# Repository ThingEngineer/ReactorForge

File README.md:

============

This repository contains hardware designs, board schematics, firmware, and software for ReactorForge, an open source high power induction heater platform.

Updates, polls, etc. on this project are being posted on the new Patreon page: [ReactorForge on Patreon](https://www.patreon.com/ReactorForge). You can also support the future of this project there as well.

For project status, official blog, and information about hardware availability visit [ReactorForge.com](https://reactorforge.com/) and be sure to read the [ReactorForge Wiki](https://github.com/joshcam/ReactorForge/wiki).

(photo: assembly of the beta ReactorCore, ReactorForge CriticalMass control board)

principal author: Joshua Campbell josh.lee.campbell@gmail.com

## Project Description
The ReactorForge project is an open source hardware platform for high power induction heating, designed for heavy use and reliable performance in real world applications.

Using fewer discreet components than most commercial induction heaters, the ReactorForge has less failure points and is easy to assemble. It is an open source project with all plans, schematics and code available under the creative commons BY-SA 4.0 license. This not only benefits the maker community and improves future designs but also makes self repair a possibility for those who have purchased kits, rather than relying on expensive factory repairs to proprietary commercial units.

The ReactorForge will be made available in a raw kit form and an ARU (Almost Ready to Use) kit that can be assembled in just a couple hours. Learn about high power electronics while building an awesome machine. The same systems in an induction heater also drive many of todays modern advances such as electric vehicles, renewable energy power inverters, cutting edge research equipment, and much more. Whether your goals are academic or you want to start using an induction heater today the ReactorForge project brings that within reach.

The ReactorForge costs thousands less than equivalent commercial models with features that are not available anywhere else. It has an easy one button/pedal interface for those that want simple to use set and forget type operation. But for those that want full control there are powerful features that let you monitor and regulate operation based on virtually any parameter. And since the entire platform is open source you have a head start to hacking the core (main control board).

(video: Test run of the ReactorForge : CriticalMass +15Kw platform)

## Safety Notice and Disclaimer
An induction heater is a high power device that should be treated with hazards similar but not limited to that of induction cooktops and welders. In addition to that, the following safety guidelines should be observed:

* Don't wear metal jewelry, especially rings near the work coil. Heating can occur a few inches from the coil depending on its geometry.
* Be cautious if you have metal implants, they too could heat up if held near the work coil.
* If you have a pacemaker or other medical implants never use or be near this machine while it is in operation.
* Keep electronics at least 12 inches from the work coil while in operation to avoid damage to these devices.
* Never touch the work coil. Although it is isolated from dangerous mains current, there is still high power present. Holding metal objects that touch or short out the work coil will not harm the unit.
* Wear appropriate PPE, including but not limited to safety glasses and gloves.

We hold no responsibility or liability for injury to person or damage to property should you choose to build and operate one of these machines. If you feel you are not qualified to build or operate an induction heater find someone qualified and willing to assist you.

## Open Source
  <br />This work is licensed under a <a rel="license" href="http://creativecommons.org/licenses/by-sa/4.0/">Creative Commons Attribution-ShareAlike 4.0 International License</a>.

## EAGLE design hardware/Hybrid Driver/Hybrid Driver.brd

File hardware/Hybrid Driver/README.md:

ReactorForge - Hybrid Driver
============

This directory contains the schematic and board file for Hybrid Driver, a dual IGBT module gate driver based on the Powerex M57962L hybrid IC.

See the Wiki for [Documentation](https://github.com/joshcam/ReactorForge/wiki/ReactorForge-Hybrid-Driver)

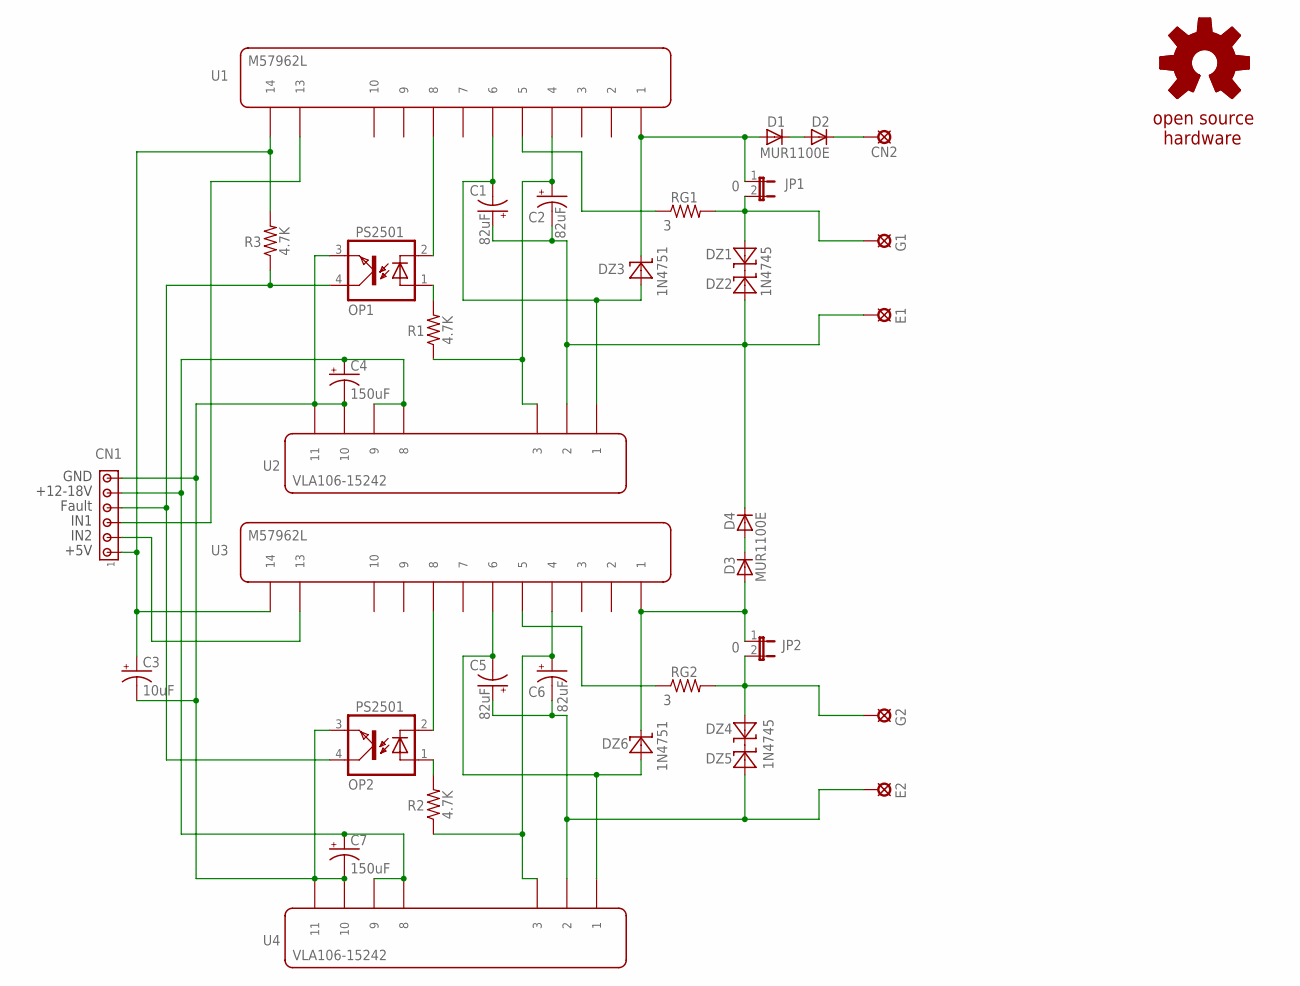
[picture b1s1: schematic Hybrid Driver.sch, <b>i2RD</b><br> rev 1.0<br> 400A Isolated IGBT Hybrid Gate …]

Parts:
C1, C2, C5, C6: 82uF; E2,5-7
C3: 10uF; E2-5
C4, C7: 150uF; E5-8,5
CN1: MTA100-6; 10X06MTA
CN2: SE14
D1, D2, D3, D4: MUR1100E; DO07
DZ1, DZ2, DZ4, DZ5: 1N4745; DIODE.4-AXIAL
DZ3, DZ6: 1N4751; DIODE.4-AXIAL
E1, E2: IGBT-PAD
G1, G2: IGBT-PAD
GOLD_ORB_SM1: OSHWLOGOLOGO8MM; OSHW_8MM
JP1, JP2: 0; JP1
OP1, OP2: PS2501; DIL04
R1, R2, R3: 4.7K; 0207/10
RG1, RG2: 3; 0309/12
U1, U3: M57962L; HYBRID-IC-IBGT-GATE-DRIVER
U2, U4: VLA106-15242; ISOLATED_DC_DC_CONVERTER

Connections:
G1: DZ1.A, G1.1, G1.2, G1.3, G1.4, G1.5, G1.6, JP1.2, RG1.2
G2: DZ4.A, G2.1, G2.2, G2.3, G2.4, G2.5, G2.6, JP2.2, RG2.2
GND: C3.-, C4.-, C7.-, CN1.1 (6), OP1.3 (EMIT), OP2.3 (EMIT), U2.10, U2.11, U4.10, U4.11
GND-E1: C1.+, C2.-, D4.C, DZ2.A, E1.1, E1.2, E1.3, E1.4, E1.5, E1.6, U2.2
GND-E2: C5.+, C6.-, DZ5.A, E2.1, E2.2, E2.3, E2.4, E2.5, E2.6, U4.2
unnamed: D1.C, D2.A
unnamed: CN2.MP, D2.C
unnamed: D1.A, DZ3.C, JP1.1, U1.1
unnamed: OP2.1 (A), R2.2
unnamed: DZ1.C, DZ2.C
unnamed: DZ4.C, DZ5.C
unnamed: C3.+, CN1.6 (1), R3.2, U1.14, U3.14
unnamed: OP2.2 (C), U3.8
unnamed: OP1.2 (C), U1.8
unnamed: OP1.1 (A), R1.2
unnamed: CN1.3 (4), OP1.4 (COL), OP2.4 (COL), R3.1
unnamed: C5.-, DZ6.A, U3.6, U4.1
unnamed: C1.-, DZ3.A, U1.6, U2.1
unnamed: C2.+, R1.1, U1.4, U2.3
unnamed: RG2.1, U3.5
unnamed: C6.+, R2.1, U3.4, U4.3
unnamed: RG1.1, U1.5
unnamed: D3.A, DZ6.C, JP2.1, U3.1
unnamed: D3.C, D4.A
unnamed: C4.+, C7.+, CN1.2 (5), U2.8, U2.9, U4.8, U4.9
unnamed: CN1.4 (3), U1.13
unnamed: CN1.5 (2), U3.13

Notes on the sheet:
GND
+12-18V
Fault
IN1
IN2
+5V

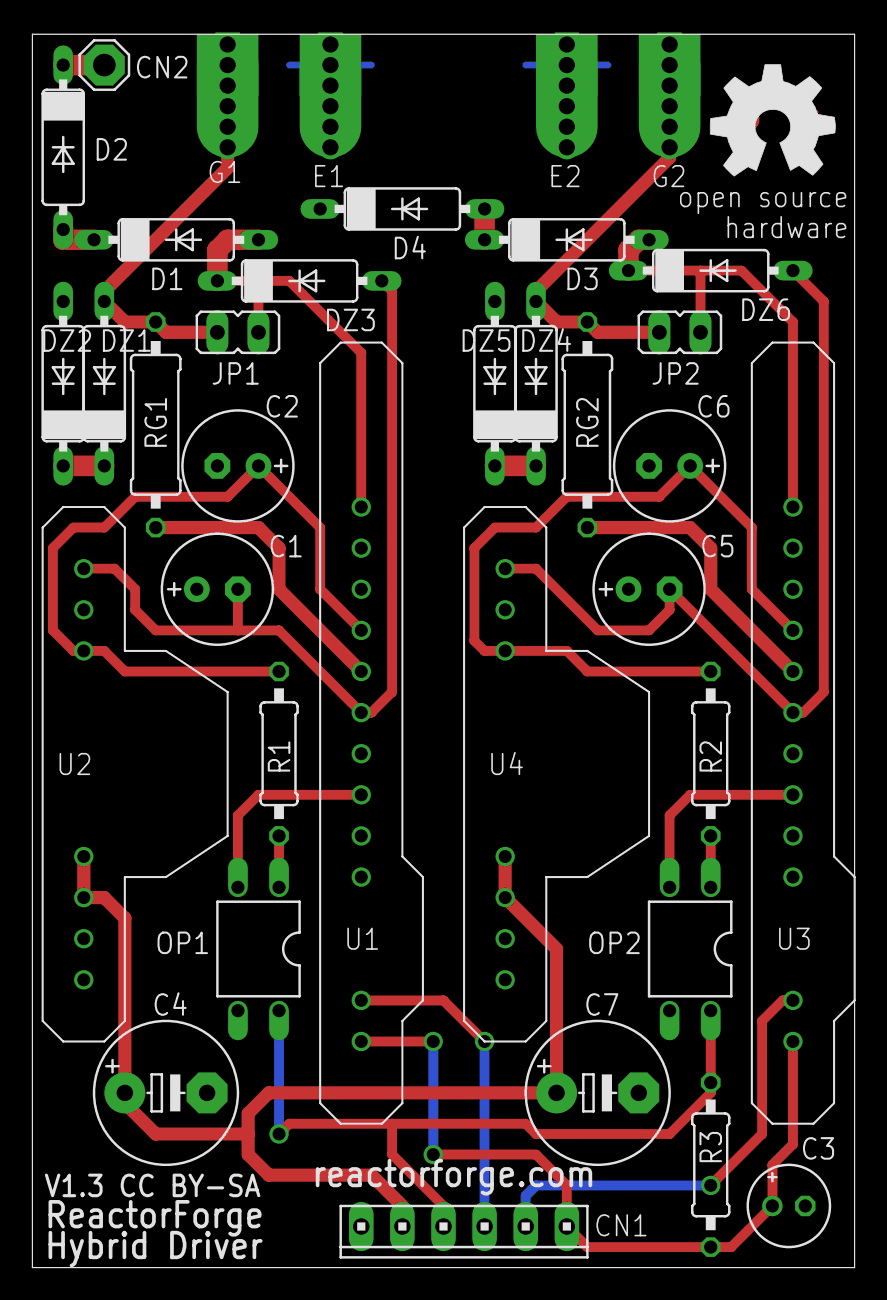
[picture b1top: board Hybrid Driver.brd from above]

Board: 2 copper layers, 50.8 x 76.2 mm, 37 parts (0 on the bottom side), 27 nets.

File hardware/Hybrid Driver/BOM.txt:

Partlist

Exported from Hybrid Driver.brd at 12/30/17 5:46 PM

EAGLE Version 8.5.1 Copyright (c) 1988-2017 Autodesk, Inc.

Assembly variant: 

Part     Value          Package                    Library     Position (inch)       Orientation

C1       82uF           E2,5-7                     resistor    (0.45 1.65)           R0
C2       82uF           E2,5-7                     resistor    (0.5 1.95)            R180
C3       10uF           E2-5                       rcl         (1.84 0.15)           R0
C4       150uF          E5-8,5                     resistor    (0.325 0.425)         R0
C5       82uF           E2,5-7                     resistor    (1.5 1.65)            R0
C6       82uF           E2,5-7                     resistor    (1.55 1.95)           R180
C7       150uF          E5-8,5                     resistor    (1.375 0.425)         R0
CN1      MTA100-6       10X06MTA                   con-amp     (1.05 0.1)            R180
CN2      SE14           SE14                       solpad      (0.175 2.925)         R0
D1       MUR1100E       DO07                       diode       (0.35 2.5)            R0
D2       MUR1100E       DO07                       diode       (0.075 2.725)         R270
D3       MUR1100E       DO07                       diode       (1.3 2.5)             R0
D4       MUR1100E       DO07                       diode       (0.9 2.6)             R0
DZ1      1N4745         DIODE.4-AXIAL              1-Custom    (0.175 2.15)          R90
DZ2      1N4745         DIODE.4-AXIAL              1-Custom    (0.075 2.15)          R90
DZ3      1N4751         DIODE.4-AXIAL              1-Custom    (0.65 2.4)            R0
DZ4      1N4745         DIODE.4-AXIAL              1-Custom    (1.225 2.15)          R90
DZ5      1N4745         DIODE.4-AXIAL              1-Custom    (1.125 2.15)          R90
DZ6      1N4751         DIODE.4-AXIAL              1-Custom    (1.65 2.425)          R0
E1       IGBT-PAD       IGBT-PAD                   1-Custom    (0.725 2.775)         R0
E2       IGBT-PAD       IGBT-PAD                   1-Custom    (1.3 2.775)           R0
G1       IGBT-PAD       IGBT-PAD                   1-Custom    (0.475 2.775)         R0
G2       IGBT-PAD       IGBT-PAD                   1-Custom    (1.55 2.775)          R0
JP1      0              JP1                        jumper      (0.5 2.275)           R90
JP2      0              JP1                        jumper      (1.575 2.275)         R90
OP1      PS2501         DIL04                      optocoupler (0.55 0.775)          R180
OP2      PS2501         DIL04                      optocoupler (1.6 0.775)           R180
R1       4.7K           0207/10                    resistor    (0.6 1.25)            R270
R2       4.7K           0207/10                    resistor    (1.65 1.25)           R270
R3       4.7K           0207/10                    resistor    (1.65 0.25)           R270
RG1      3              0309/12                    resistor    (0.3 2.05)            R90
RG2      3              0309/12                    resistor    (1.35 2.05)           R90
U1       M57962L        HYBRID-IC-IBGT-GATE-DRIVER 1-Custom    (0.65 2.25)           R270
U2       VLA106-15242   ISOLATED_DC_DC_CONVERTER   1-Custom    (-0.025 1.85)         R270
U3       M57962L        HYBRID-IC-IBGT-GATE-DRIVER 1-Custom    (1.7 2.25)            R270
U4       VLA106-15242   ISOLATED_DC_DC_CONVERTER   1-Custom    (1 1.85)              R270

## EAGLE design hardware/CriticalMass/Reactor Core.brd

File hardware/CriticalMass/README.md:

ReactorForge - CriticalMass
============

CriticalMass is the general purpose base unit. Built to run on 240V single phase and be usable on a practical level with large work pieces.

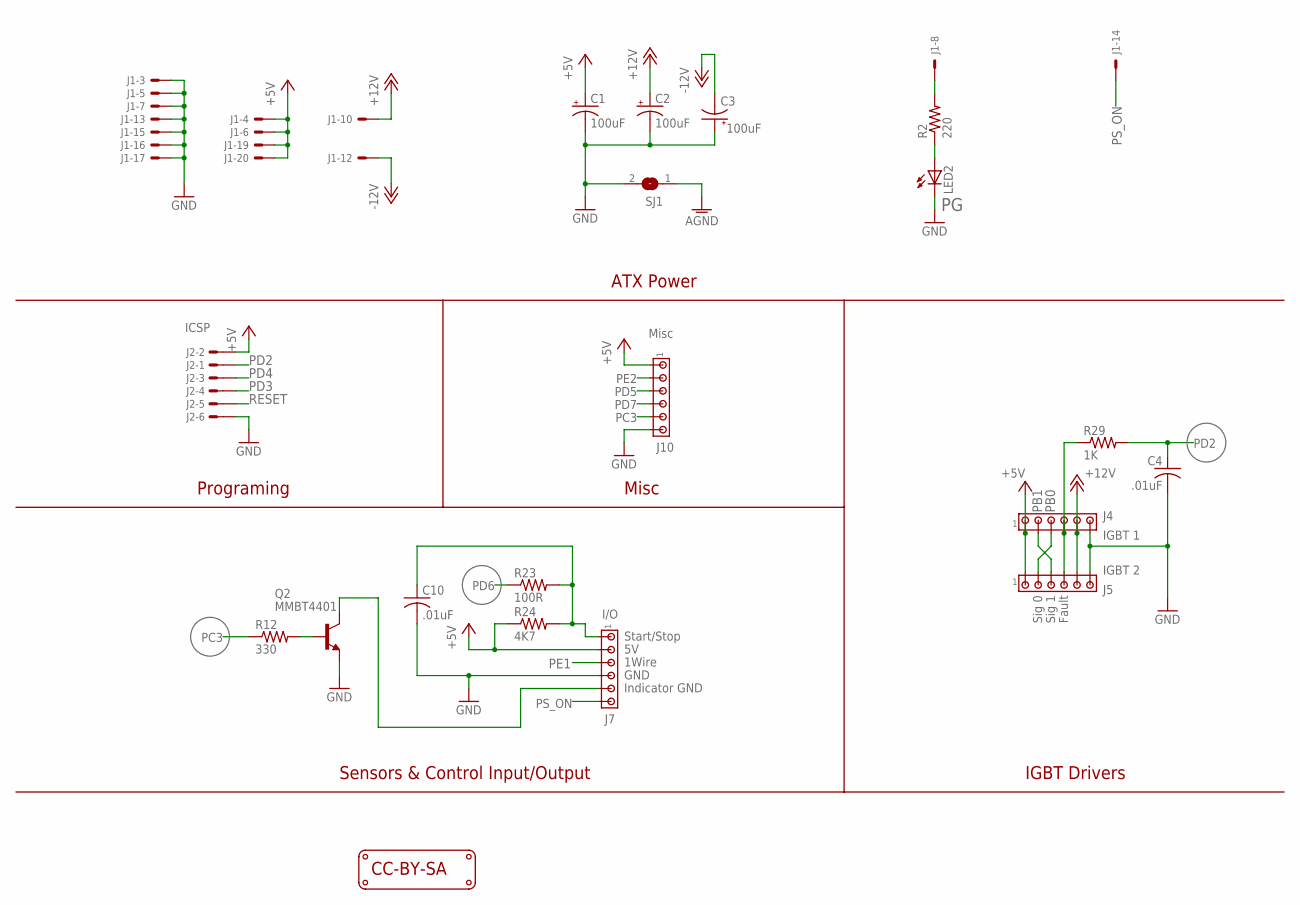
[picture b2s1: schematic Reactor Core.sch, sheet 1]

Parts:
C1, C2, C3: 100uF; E2-5
C4: .01uF; C1206
C10: .01uF; C1206K
J1: ATX Power; 5566-20; MPN 39-29-9206
J2: ICSP; 057-006-1
J4: IGBT 1; 10X06MTA
J5: IGBT 2; 10X06MTA
J7: I/O; 10X06MTA
J10: Misc; 10X06MTA
LED2: LEDCHIPLED_1206; CHIPLED_1206
LOGO1: LOGO_CC-BY-SA
Q2: MMBT4401; SOT23
R2: 220; R1206
R12: 330; R1206
R23: 100R; R1206
R24: 4K7; R1206
R29: 1K; R1206
SJ1: 0; SJ

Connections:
+5V: C1.+, J1.4, J1.6, J1.19, J1.20, J2.2, J4.6 (1), J5.6 (1), J7.5 (2), J10.6 (1), R24.1; also elsewhere on the board
+12V: C2.+, J1.10, J4.2 (5), J5.2 (5); also elsewhere on the board
-12V: C3.-, J1.12; also elsewhere on the board
AGND: SJ1.1; also elsewhere on the board
FAULT: J4.3 (4), J5.3 (4), R29.1
GND: C1.-, C2.-, C3.+, C4.2, C10.2, J1.3, J1.5, J1.7, J1.13, J1.15, J1.16, J1.17, J2.6, J4.1 (6), J5.1 (6), J7.3 (4), J10.1 (6), LED2.C, Q2.2 (E), SJ1.2; also elsewhere on the board
unnamed: LED2.A, R2.1
unnamed: J7.2 (5), Q2.3 (C)
unnamed: Q2.1 (B), R12.2
unnamed: C10.1, J7.6 (1), R23.2, R24.2
PB0: J4.4 (3), J5.5 (2); also elsewhere on the board
PB1: J4.5 (2), J5.4 (3); also elsewhere on the board
PC3: J10.2 (5), R12.1; also elsewhere on the board
PD2: C4.1, J2.1, R29.2; also elsewhere on the board
PD3: J2.4; also elsewhere on the board
PD4: J2.3; also elsewhere on the board
PD5: J10.4 (3); also elsewhere on the board
PD6: R23.1; also elsewhere on the board
PD7: J10.3 (4); also elsewhere on the board
PE1: J7.4 (3); also elsewhere on the board
PE2: J10.5 (2); also elsewhere on the board
PG: J1.8, R2.2
PS_ON: J1.14, J7.1 (6)
RESET: J2.5; also elsewhere on the board

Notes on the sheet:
ATX Power
Programing
Sensors & Control Input/Output
Start/Stop
1Wire
Indicator GND
Misc
GND
IGBT Drivers
Fault
Sig 1
Sig 0

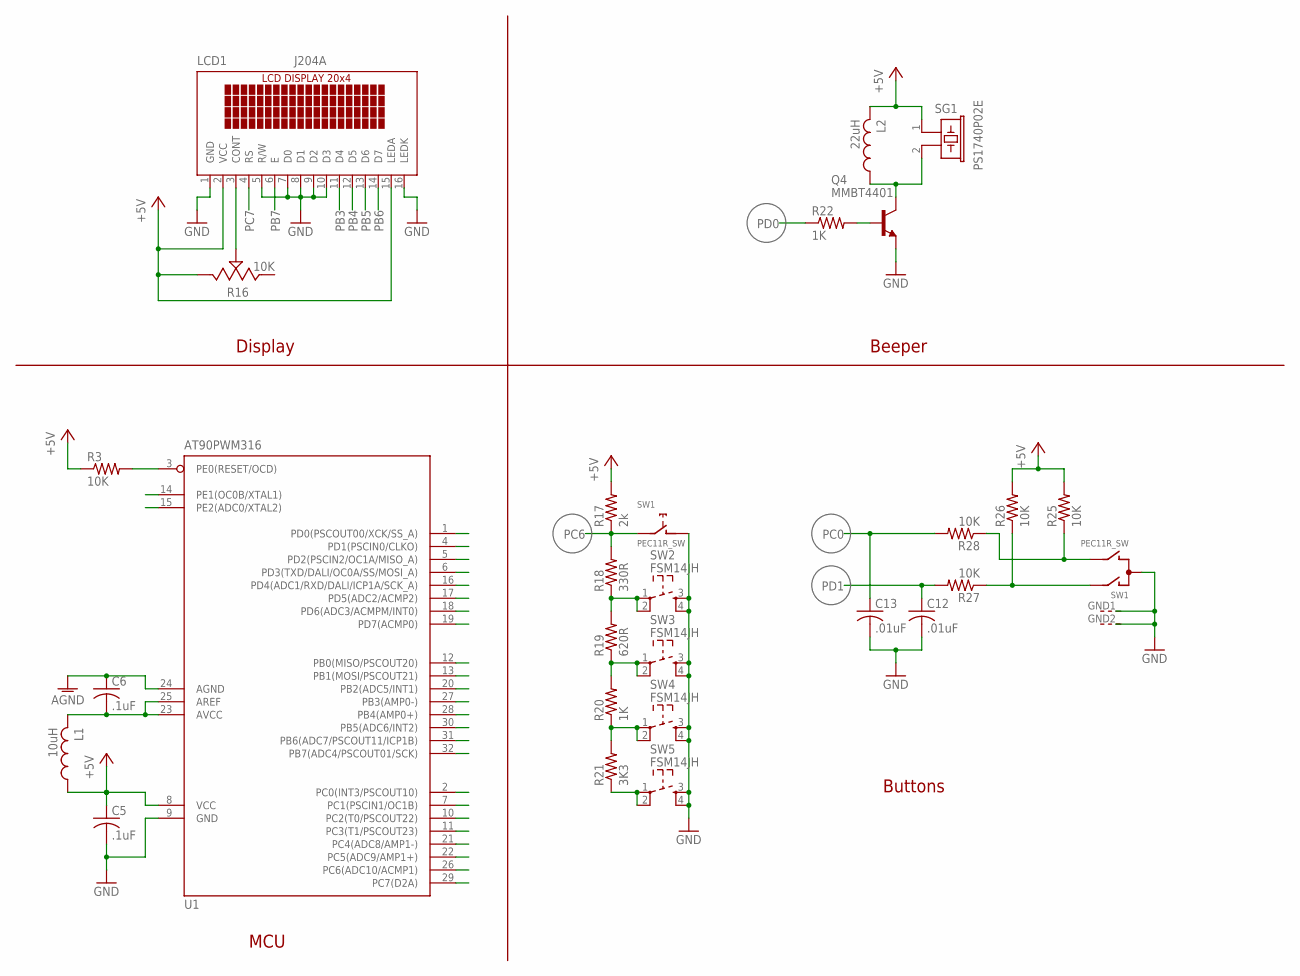
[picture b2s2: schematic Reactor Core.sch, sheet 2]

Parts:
C5, C6: .1uF; C1206K
C12, C13: .01uF; C1206K
L1: 10uH; L3225P
L2: 22uH; L3225P
LCD1: J204A; LCD-20X4
Q4: MMBT4401; SOT23
R3, R27, R28: 10K; R1206
R16: 10K; TRIMMER_3314G
R17: 2k; R1206
R18: 330R; R1206
R19: 620R; R1206
R20, R22: 1K; R1206
R21: 3K3; R1206
R25, R26: 10K; M1206
SG1: PS1740P02E; F/EE17P; MPN PS1740P02E
SW1: PEC11R_SW; BOURNS_PEC11R_SW
SW2, SW3, SW4, SW5: FSM14JH; SW_TACTILE_TOP_ACTIVATED
U1: AT90PWM316; SOIC-32

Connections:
+5V: C5.1, L1.1, L2.2, LCD1.2 (VCC), LCD1.15 (LEDA), R3.1, R16.3, R17.2, R25.2, R26.2, SG1.1, U1.8 (VCC); also elsewhere on the board
AGND: C6.1, U1.24 (AGND); also elsewhere on the board
AVCC: C6.2, L1.2, U1.23 (AVCC), U1.25 (AREF)
GND: C5.2, C12.2, C13.2, LCD1.1 (GND), LCD1.5 (R/W), LCD1.7 (D0), LCD1.8 (D1), LCD1.9 (D2), LCD1.10 (D3), LCD1.16 (LEDK), Q4.2 (E), SW1.C, SW1.GND1 (G), SW1.GND2 (G), SW1.S (1), SW2.3, SW2.4, SW3.3, SW3.4, SW4.3, SW4.4, SW5.3, SW5.4, U1.9 (GND); also elsewhere on the board
unnamed: LCD1.3 (CONT), R16.2
unnamed: L2.1, Q4.3 (C), SG1.2
unnamed: Q4.1 (B), R22.2
unnamed: R25.1, R28.1, SW1.B
unnamed: R26.1, R27.1, SW1.A
unnamed: R21.1, SW5.1, SW5.2
unnamed: R18.1, R19.2, SW2.1, SW2.2
unnamed: R19.1, R20.2, SW3.1, SW3.2
unnamed: R20.1, R21.2, SW4.1, SW4.2
PB0: U1.12 (PB0(MISO/PSCOUT20)); also elsewhere on the board
PB1: U1.13 (PB1(MOSI/PSCOUT21)); also elsewhere on the board
PB2: U1.20 (PB2(ADC5/INT1)); also elsewhere on the board
PB3: LCD1.11 (D4), U1.27 (PB3(AMP0-))
PB4: LCD1.12 (D5), U1.28 (PB4(AMP0+))
PB5: LCD1.13 (D6), U1.30 (PB5(ADC6/INT2))
PB6: LCD1.14 (D7), U1.31 (PB6(ADC7/PSCOUT11/ICP1B))
PB7: LCD1.6 (E), U1.32 (PB7(ADC4/PSCOUT01/SCK))
PC0: C13.1, R28.2, U1.2 (PC0(INT3/PSCOUT10))
PC1: U1.7 (PC1(PSCIN1/OC1B)); also elsewhere on the board
PC2: U1.10 (PC2(T0/PSCOUT22)); also elsewhere on the board
PC3: U1.11 (PC3(T1/PSCOUT23)); also elsewhere on the board
PC4: U1.21 (PC4(ADC8/AMP1-)); also elsewhere on the board
PC5: U1.22 (PC5(ADC9/AMP1+)); also elsewhere on the board
PC6: R17.1, R18.2, SW1.W (2), U1.26 (PC6(ADC10/ACMP1))
PC7: LCD1.4 (RS), U1.29 (PC7(D2A))
PD0: R22.1, U1.1 (PD0(PSCOUT00/XCK/SS_A))
PD1: C12.1, R27.2, U1.4 (PD1(PSCIN0/CLKO))
PD2: U1.5 (PD2(PSCIN2/OC1A/MISO_A)); also elsewhere on the board
PD3: U1.6 (PD3(TXD/DALI/OC0A/SS/MOSI_A)); also elsewhere on the board
PD4: U1.16 (PD4(ADC1/RXD/DALI/ICP1A/SCK_A)); also elsewhere on the board
PD5: U1.17 (PD5(ADC2/ACMP2)); also elsewhere on the board
PD6: U1.18 (PD6(ADC3/ACMPM/INT0)); also elsewhere on the board
PD7: U1.19 (PD7(ACMP0)); also elsewhere on the board
PE1: U1.14 (PE1(OC0B/XTAL1)); also elsewhere on the board
PE2: U1.15 (PE2(ADC0/XTAL2)); also elsewhere on the board
RESET: R3.2, U1.3 (PE0(RESET/OCD)); also elsewhere on the board

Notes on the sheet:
MCU
Display
Buttons
Beeper

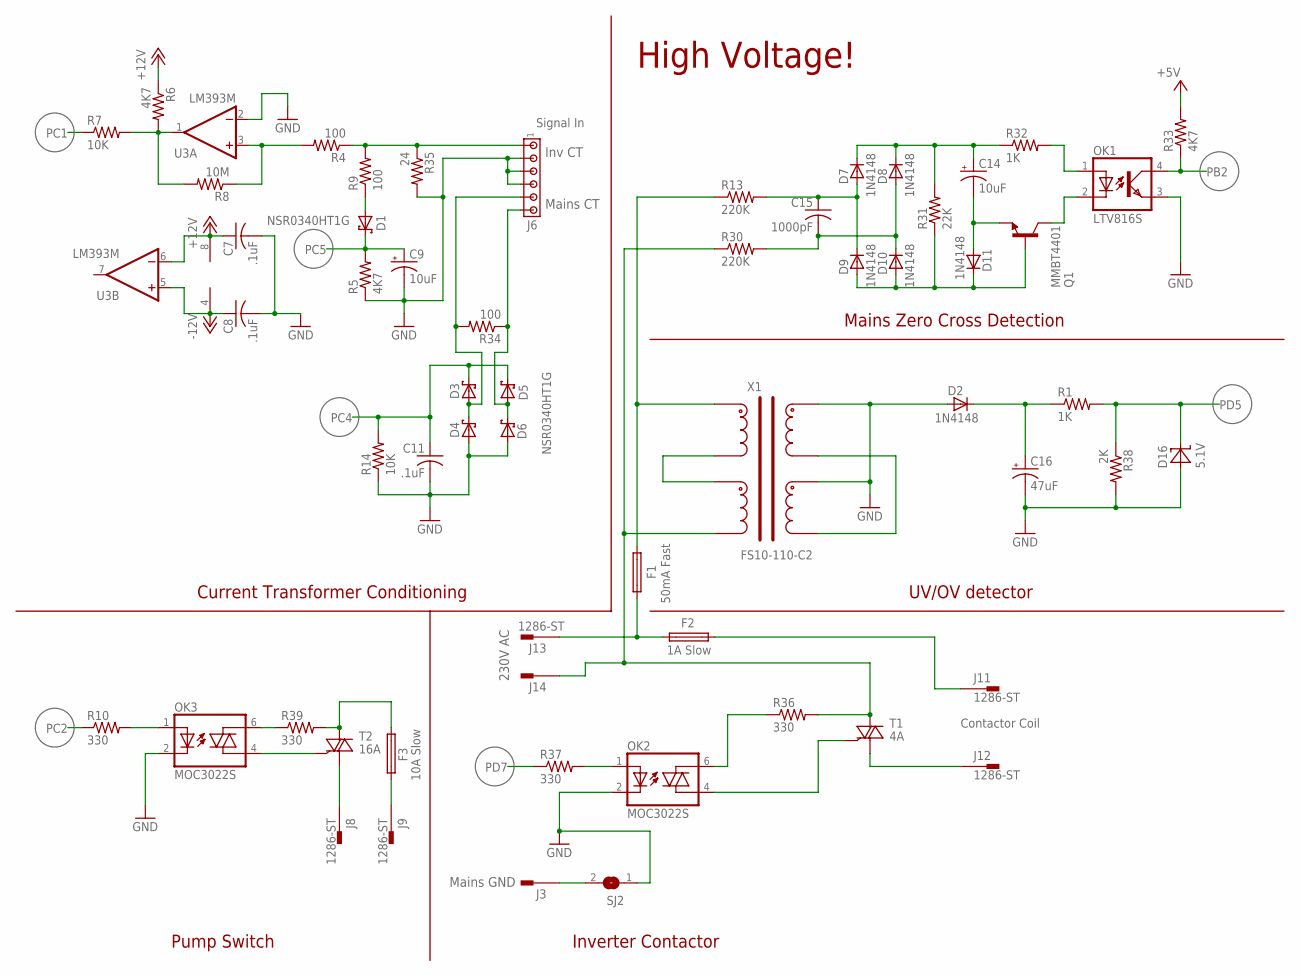
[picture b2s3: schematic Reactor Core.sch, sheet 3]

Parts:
C7, C8, C11: .1uF; C1206
C9, C14: 10uF; 153CLV-0405
C15: 1000pF; C1206
C16: 47uF; 153CLV-0605
D1, D3, D4, D5, D6: NSR0340HT1G; SOD-323
D2, D7, D8, D9, D10, D11: 1N4148; SOD-123
D16: 5.1V; SOD-323
F1: 50mA Fast; TR5; MPN MRF 50
F2: 1A Slow; FC211-5X20
F3: 10A Slow; FC211-5X20
J3, J8, J9, J11, J12, J13, J14: 1286-ST; 62409-1
J6: Signal In; 10X06MTA
OK1: LTV816S; SMD4
OK2: MOC3022S; 6-SMD
OK3: MOC3022S; 6-SMD; MPN MOC3022S
Q1: MMBT4401; SOT23
R1: 1K; R1206; MPN RNCP1206FTD100R
R4, R9: 100; R1206
R5, R6, R33: 4K7; R1206
R7, R14: 10K; R1206
R8: 10M; R1206
R10: 330; M1206
R13, R30: 220K; R1206
R31: 22K; R1206
R32: 1K; R1206
R34: 100; R1206; MPN RNCP1206FTD100R
R35: 24; R2512; MPN 352124RFT
R36, R37, R39: 330; R1206
R38: 2K; R1206; MPN RNCP1206FTD100R
SJ2: 0; SJ
T1: 4A; DPAK-TRIAC
T2: 16A; DPAK-TRIAC; MPN T1635-700G-TR
U3: LM393M; SO08; MPN LM393M
X1: FS10-110-C2

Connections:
240A: F1.1, F2.1A (1), F2.1B (1), J13.A1, J13.A2
240B: J14.A1, J14.A2, R30.1, R36.2, T1.A2, X1.P$4
+5V: R33.2; also elsewhere on the board
+12V: C7.1, R6.1, U3.6 (-IN), U3.8 (V+); also elsewhere on the board
-12V: C8.1, U3.4 (V-), U3.5 (+IN); also elsewhere on the board
GND: C7.2, C8.2, C9.-, C11.2, C16.-, D2.A, D4.A, D6.A, D16.A, J6.3 (4), J6.4 (3), J6.5 (2), OK1.3 (EMIT), OK2.2 (C), OK3.2 (C), R5.1, R14.1, R35.2, R38.2, SJ2.1, U3.2 (-IN), X1.P$5, X1.P$7; also elsewhere on the board
MGND: J3.A1, J3.A2, SJ2.2
unnamed: OK3.1 (A), R10.2
unnamed: OK3.6 (A2), R39.1
unnamed: OK2.1 (A), R37.2
unnamed: J6.6 (1), R4.1, R9.2, R35.1
unnamed: F3.2A (2), F3.2B (2), R39.2, T2.A2
unnamed: R4.2, R8.1, U3.3 (+IN)
unnamed: OK3.4 (A1), T2.G
unnamed: R6.2, R7.2, R8.2, U3.1 (OUT)
unnamed: D1.A, R9.1
unnamed: D3.A, D4.C, J6.2 (5), R34.2
unnamed: D5.A, D6.C, J6.1 (6), R34.1
unnamed: X1.P$6, X1.P$8
unnamed: X1.P$2, X1.P$3
unnamed: C15.1, D7.A, D9.C, R13.2
unnamed: C15.2, D8.A, D10.C, R30.2
unnamed: OK2.6 (A2), R36.1
unnamed: OK2.4 (A1), T1.G
unnamed: D9.A, D10.A, D11.C, Q1.1 (B), R31.1
unnamed: C14.+, D7.C, D8.C, R31.2, R32.1
unnamed: C14.-, D11.A, Q1.2 (E)
unnamed: J12.A1, J12.A2, T1.A1
unnamed: OK1.1 (A), R32.2
unnamed: OK1.2 (C), Q1.3 (C)
unnamed: F2.2A (2), F2.2B (2), J11.A1, J11.A2
unnamed: J8.A1, J8.A2, T2.A1
unnamed: C16.+, D2.C, R1.1
unnamed: F1.2, R13.1, X1.P$1
unnamed: F3.1A (1), F3.1B (1), J9.A1, J9.A2
PB2: OK1.4 (COL), R33.1; also elsewhere on the board
PC1: R7.1; also elsewhere on the board
PC2: R10.1; also elsewhere on the board
PC4: C11.1, D3.C, D5.C, R14.2; also elsewhere on the board
PC5: C9.+, D1.C, R5.2; also elsewhere on the board
PD5: D16.C, R1.2, R38.1; also elsewhere on the board
PD7: R37.1; also elsewhere on the board

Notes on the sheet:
Inv CT
Mains CT
UV/OV detector
230V AC
Mains Zero Cross Detection
Current Transformer Conditioning
Contactor Coil
Pump Switch
Inverter Contactor
High Voltage!
Mains GND

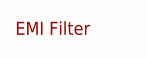
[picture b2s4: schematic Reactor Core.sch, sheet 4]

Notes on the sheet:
EMI Filter

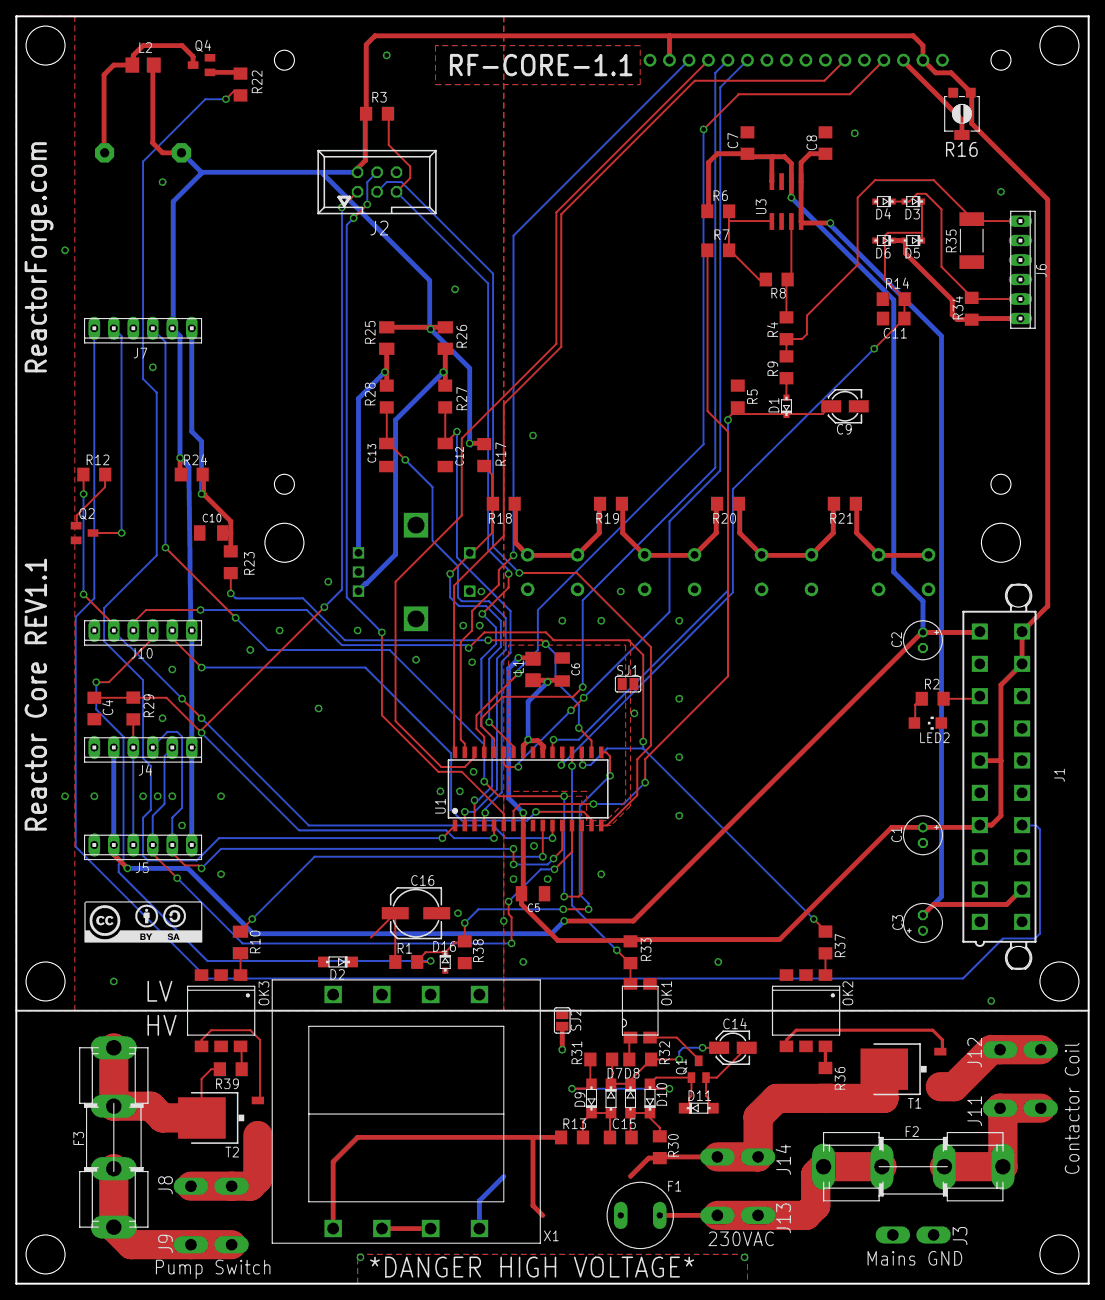
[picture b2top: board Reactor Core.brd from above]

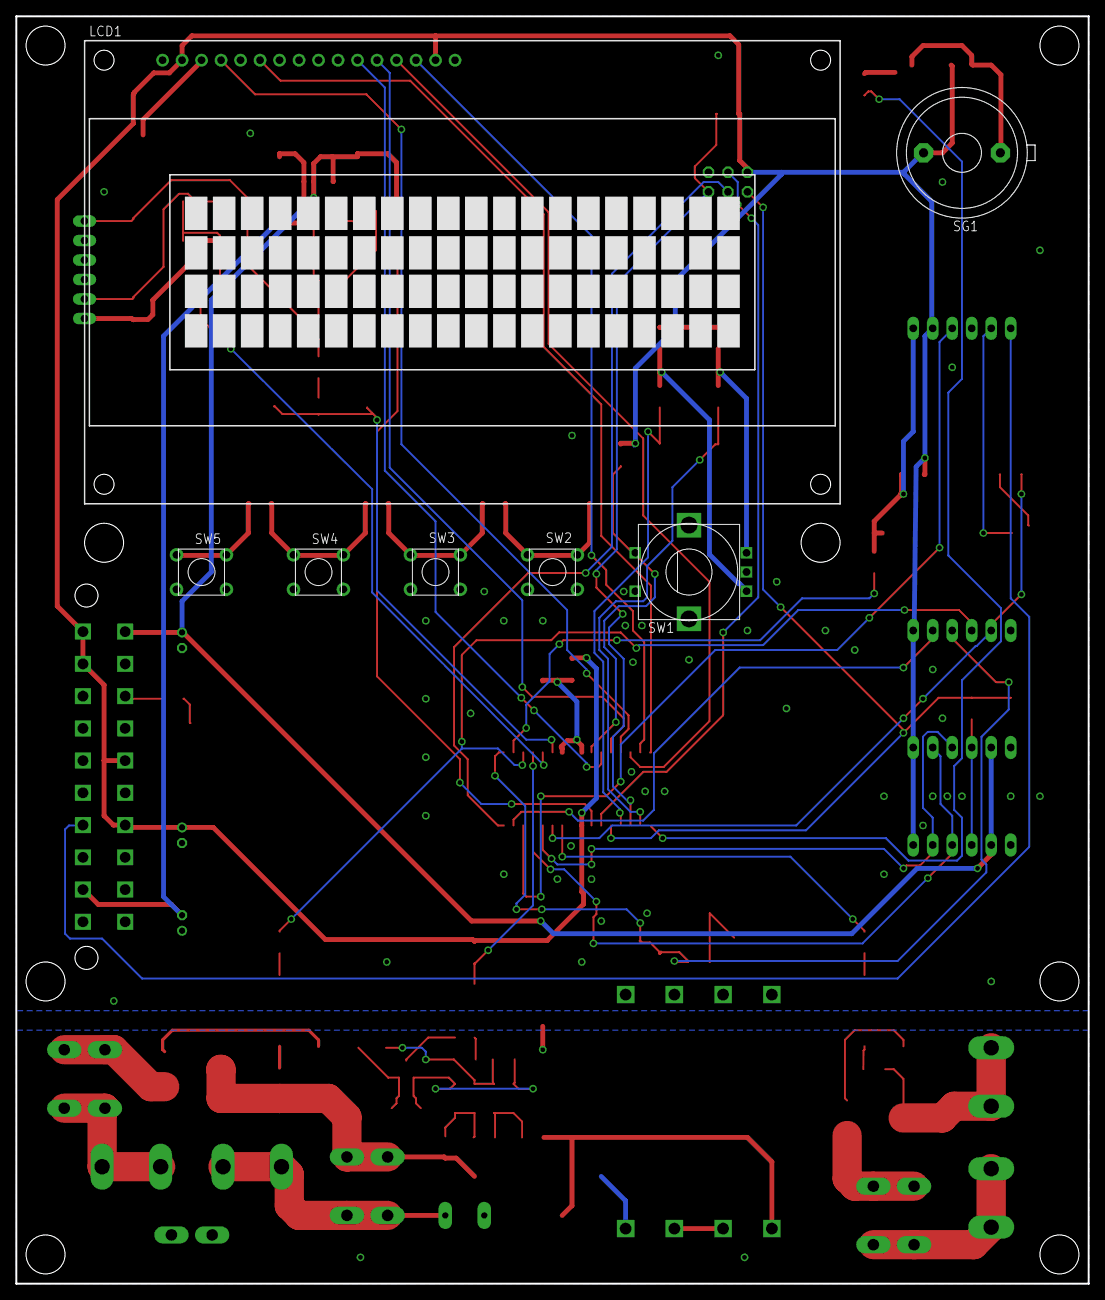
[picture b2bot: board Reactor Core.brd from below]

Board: 2 copper layers, 139.7 x 165.1 mm, 106 parts (7 on the bottom side), 80 nets.

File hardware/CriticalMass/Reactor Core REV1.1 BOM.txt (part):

Partlist exported from /Users/Josh/Dropbox/Projects/eagle/Induction Heaters/CriticalMass/Reactor Core.sch at 9/25/18 8:56 PM

Part  Value         Device                   Package                  Description                                       MF                        MPN                OC_FARNELL OC_NEWARK PN_DIGI-KEY          
C1    100uF         CPOL-USE2-5              E2-5                     POLARIZED CAPACITOR, American symbol                                                                                                     
C2    100uF         CPOL-USE2-5              E2-5                     POLARIZED CAPACITOR, American symbol                                                                                                     
C3    100uF         CPOL-USE2-5              E2-5                     POLARIZED CAPACITOR, American symbol                                                                                                     
C4    .01uF         C-USC1206                C1206                    CAPACITOR, American symbol                                                                                                               
C5    .1uF          C-USC1206K               C1206K                   CAPACITOR, American symbol                                                                                                               
C6    .1uF          C-USC1206K               C1206K                   CAPACITOR, American symbol                                                                                                               
C7    .1uF          C-USC1206                C1206                    CAPACITOR, American symbol                                                                                                               
C8    .1uF          C-USC1206                C1206                    CAPACITOR, American symbol                                                                                                               
C9    10uF          CPOL-US153CLV-0405       153CLV-0405              POLARIZED CAPACITOR, American symbol                                                                                                     
C10   .01uF         C-USC1206K               C1206K                   CAPACITOR, American symbol                                                                                                               
C11   .1uF          C-USC1206                C1206                    CAPACITOR, American symbol                                                                                                               
C12   .01uF         C-USC1206K               C1206K                   CAPACITOR, American symbol                                                                                                               
C13   .01uF         C-USC1206K               C1206K                   CAPACITOR, American symbol                                                                                                               
C14   10uF          CPOL-US153CLV-0405       153CLV-0405              POLARIZED CAPACITOR, American symbol                                                                                                     
C15   1000pF        C-USC1206                C1206                    CAPACITOR, American symbol                                                                                                               
C16   47uF          CPOL-US153CLV-0605       153CLV-0605              POLARIZED CAPACITOR, American symbol                                                                                                     
D1    NSR0340HT1G   NSR0340HT1G              SOD-323                  NSR0340HT1G                                                                                                                              
D2    1N4148        1N4148                   SOD-123                  1N4148                                                                                                                                   
D3    NSR0340HT1G   NSR0340HT1G              SOD-323                  NSR0340HT1G                                                                                                                              
D4    NSR0340HT1G   NSR0340HT1G              SOD-323                  NSR0340HT1G                                                                                                                              
D5    NSR0340HT1G   NSR0340HT1G              SOD-323                  NSR0340HT1G                                                                                                                              
D6    NSR0340HT1G   NSR0340HT1G              SOD-323                  NSR0340HT1G                                                                                                                              
D7    1N4148        1N4148                   SOD-123                  1N4148                                                                                                                                   
D8    1N4148        1N4148                   SOD-123                  1N4148                                                                                                                                   
D9    1N4148        1N4148                   SOD-123                  1N4148                                                                                                                                   
D10   1N4148        1N4148                   SOD-123                  1N4148                                                                                                                                   
D11   1N4148        1N4148                   SOD-123                  1N4148                                                                                                                                   
D16   5.1V          MM3Z5V1ST1G              SOD-323                  MM3Z5V1ST1G                                       5.1V 200MW                MM3Z5V1ST1G                             MM3Z5V1ST1GOSCT-ND   
F1    50mA Fast     TR5                      TR5                      FUSE                                              Bel Fuse Inc              MRF 50             unknown    unknown   507-1715-ND          
F2    1A Slow       FC211-5X20               FC211-5X20               FC 211                                                                                                                                   
F3    10A Slow      FC211-5X20               FC211-5X20               FC 211                                                                                                                                   
J1    ATX Power     5566-20                  5566-20                  Mini FIT connector 20 pol                                                   39-29-9206         unknown    unknown   2M3873-ND            
J2    ICSP          057-006-1                057-006-1                CONNECTOR                                                                                      unknown    unknown                        
J3    1286-ST       PIN262409-1              62409-1                  Flachstecker Typ Tyco/Electronics/AMP TAB, FASTON                                              unknown    unknown                        
J4    IGBT 1        MTA06-100                10X06MTA                 AMP connector                                                                                                                            
J5    IGBT 2        MTA06-100                10X06MTA                 AMP connector                                                                                                                            
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

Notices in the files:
hardware/Hybrid Driver/Hybrid Driver.brd:
V1.3 CC BY-SA
parts and their libraries:
1-Custom: LICENSE: CC-BY-SA
